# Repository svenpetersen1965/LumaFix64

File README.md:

# LumaFix64
The LumaFix64 is not my design. It is based on <a href="https://www.lemon64.com/forum/viewtopic.php?t=40570&start=375">e5frog's LumaFix64 design</a>, which was released in March 7th, 2018 in the Lemon64.com forum. The changes in my design are:
* No through hole parts
* PCB a little bit narrower
* the Chroma potentiometer (CHR) can be replaced with a fix resistor or just a solder bridge

The Chroma potentiometer is IMHO not required, because it is not desirable to reduce the chominance level before the composite video signal is generated in the RF modulator. 

The LumaFix64 requires the precision round pin strips, because those are narrow enough not to break the socket of VIC-II chip. Since these pin strips are fragile, the LumaFix64 has to be handle with care.

I have received the permission of e5frog for publishing these files in this github repository (see screen shot in the "pictures" folder).

# BOM value
The calculation of the BOM values is available in the EXCEL folder. The total BOM value is 9,63€ (May 2020). This includes the Chroma pot and domestic pin strips. It is possible to save money on both, when ordering overseas.

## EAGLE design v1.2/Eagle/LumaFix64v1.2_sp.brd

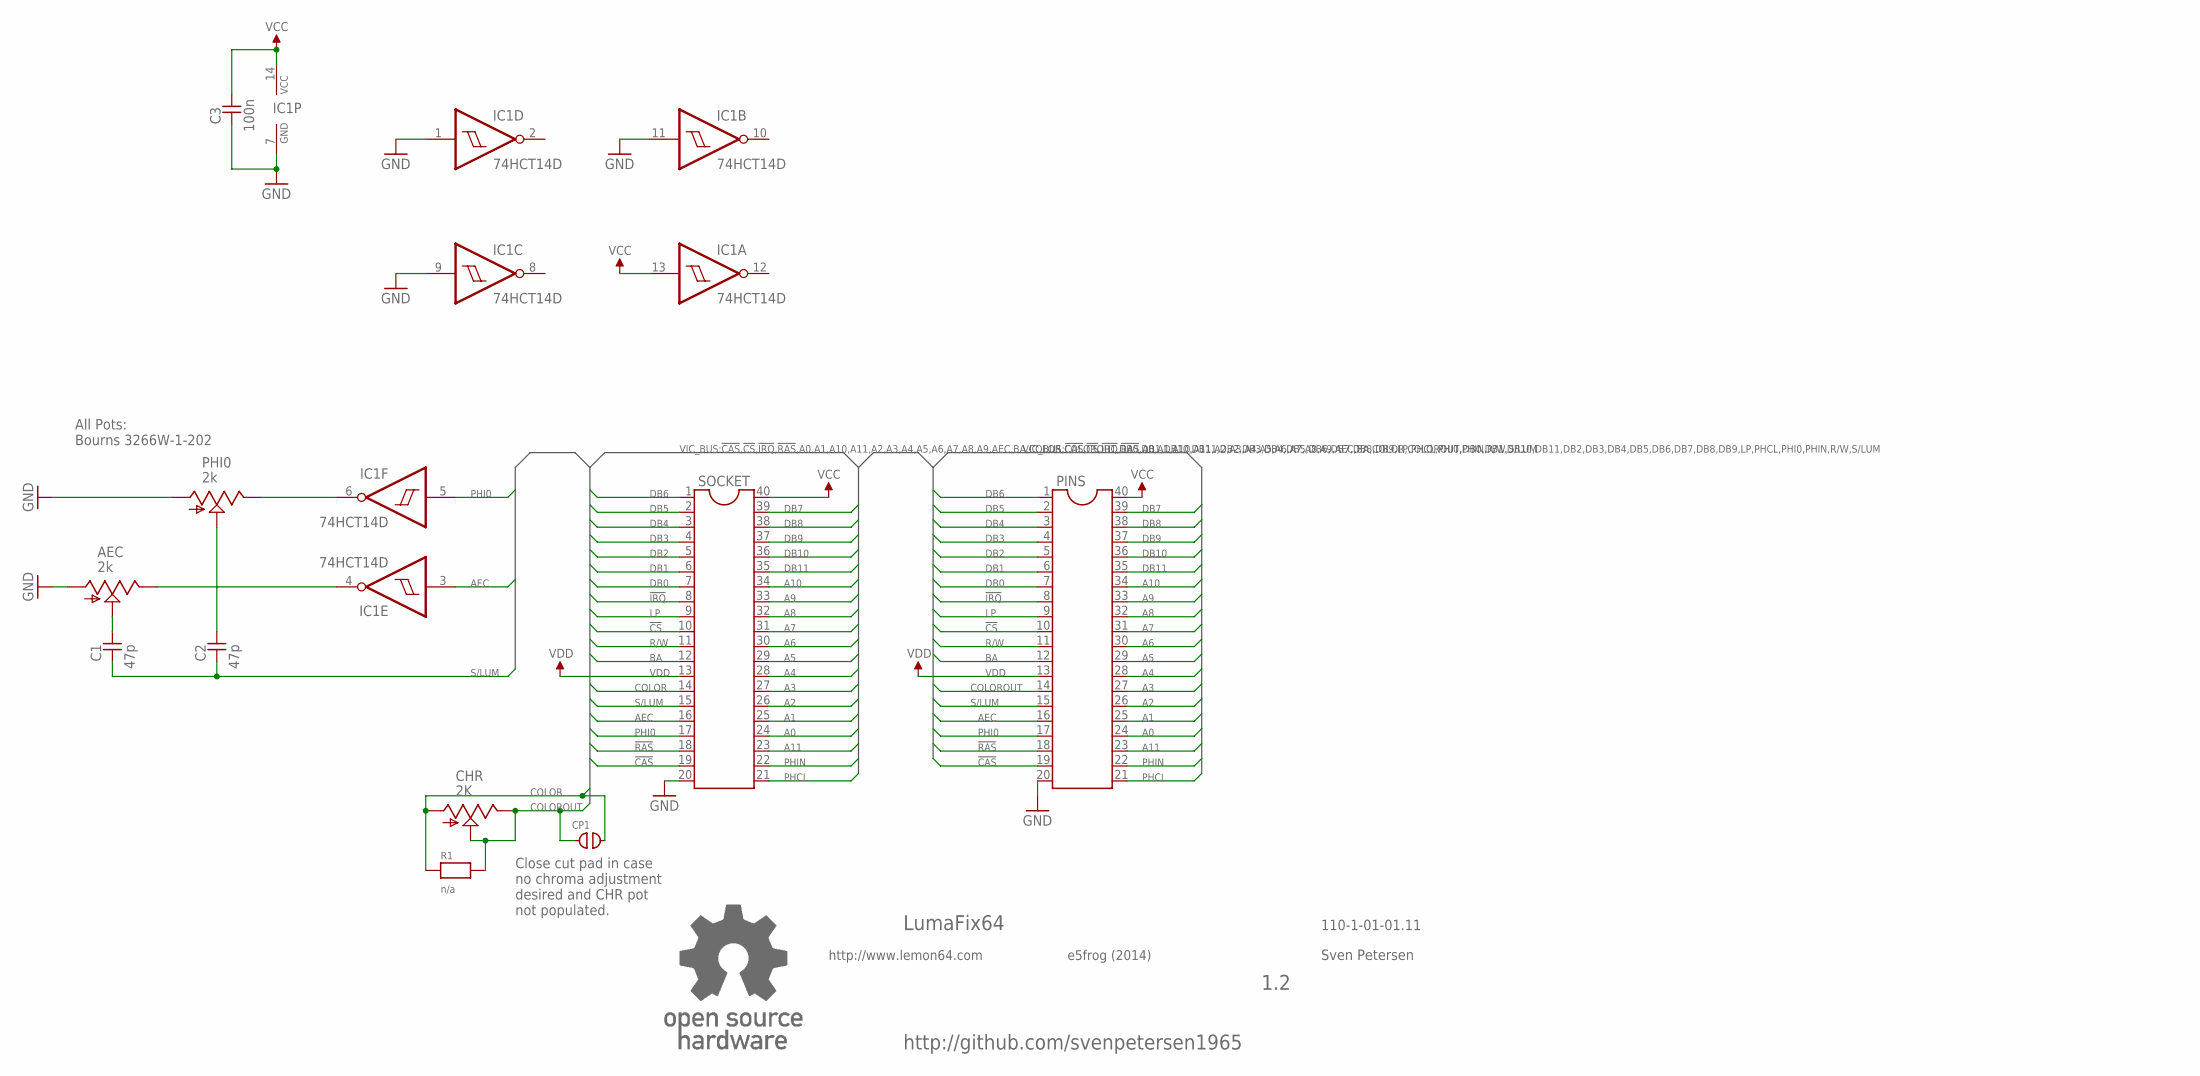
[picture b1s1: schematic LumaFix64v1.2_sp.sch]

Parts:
AEC: 2k; POT_B64W
C1, C2: 47p; 0805
C3: 100n; 0805
CHR: 2K; POT_B64W
CP1: OPEN; CP_OP
IC1: 74HCT14D; SO14
PHI0: 2k; POT_B64W
PINS: IC-PACKAGE_DIL40_10120540; BLK_10120540_2X20
R1: n/a; 0805
SOCKET: IC-PACKAGE_DIL40GS40P; GS40P
U$13: OPEN_SOURCE_HW; OPENHW

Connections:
!CAS: PINS.19, SOCKET.19
!CS: PINS.10, SOCKET.10
!IRQ: PINS.8, SOCKET.8
!RAS: PINS.18, SOCKET.18
A0: PINS.24, SOCKET.24
A1: PINS.25, SOCKET.25
A2: PINS.26, SOCKET.26
A3: PINS.27, SOCKET.27
A4: PINS.28, SOCKET.28
A5: PINS.29, SOCKET.29
A6: PINS.30, SOCKET.30
A7: PINS.31, SOCKET.31
A8: PINS.32, SOCKET.32
A9: PINS.33, SOCKET.33
A10: PINS.34, SOCKET.34
A11: PINS.23, SOCKET.23
AEC: IC1.3 (I), PINS.16, SOCKET.16
BA: PINS.12, SOCKET.12
COLOR: CHR.A, CP1.2, R1.1, SOCKET.14
COLOROUT: CHR.E, CHR.S, CP1.1, PINS.14, R1.2
DB0: PINS.7, SOCKET.7
DB1: PINS.6, SOCKET.6
DB2: PINS.5, SOCKET.5
DB3: PINS.4, SOCKET.4
DB4: PINS.3, SOCKET.3
DB5: PINS.2, SOCKET.2
DB6: PINS.1, SOCKET.1
DB7: PINS.39, SOCKET.39
DB8: PINS.38, SOCKET.38
DB9: PINS.37, SOCKET.37
DB10: PINS.36, SOCKET.36
DB11: PINS.35, SOCKET.35
GND: AEC.A, C3.1, IC1.1 (I), IC1.7 (GND), IC1.9 (I), IC1.11 (I), PHI0.A, PINS.20, SOCKET.20
LP: PINS.9, SOCKET.9
unnamed: AEC.S, C1.2
unnamed: C2.2, PHI0.S
unnamed: AEC.E, IC1.4 (O)
unnamed: IC1.6 (O), PHI0.E
PHCL: PINS.21, SOCKET.21
PHI0: IC1.5 (I), PINS.17, SOCKET.17
PHIN: PINS.22, SOCKET.22
R/W: PINS.11, SOCKET.11
S/LUM: C1.1, C2.1, PINS.15, SOCKET.15
VCC: C3.2, IC1.13 (I), IC1.14 (VCC), PINS.40, SOCKET.40
VDD: PINS.13, SOCKET.13

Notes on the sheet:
LumaFix64
http://www.lemon64.com
e5frog (2014)
1.2
110-1-01-01.11
Sven Petersen
All Pots: Bourns 3266W-1-202
Close cut pad in case no chroma adjustment desired and CHR pot not populated.
http://github.com/svenpetersen1965

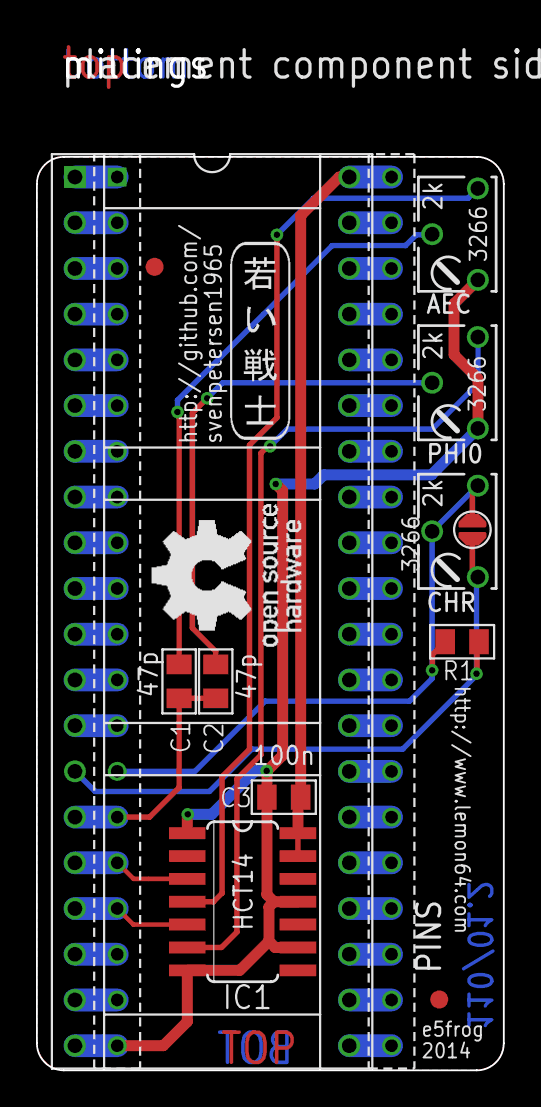
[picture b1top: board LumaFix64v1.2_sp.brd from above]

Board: 2 copper layers, 25.9 x 57.4 mm, 17 parts (0 on the bottom side), 45 nets.

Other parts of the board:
U$7: 2LAYER
U$9: PCB-TITLE/
U$10, U$11: SMD_REF_R1MM
U$12: SVEN_TAG

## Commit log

2020-08-11 Silk Screen Update
2020-08-17 PicknPlace in mm and inch
